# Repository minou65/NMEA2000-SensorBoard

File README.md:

# NMEA2000 Sensorboard

A universal PCB designed to support multiple NMEA 2000 sensor projects based on an ESP32 D1 Mini and an MCP2562 CAN bus transceiver. The board provides a 5 V regulated supply from the NMEA bus power line and exposes connectors for various sensors.

## Important Hint

Although the term NMEA2000 is used here, the software and device are **not certified NMEA2000 products** and have not passed any official approval process.
There is a possibility that the software or hardware does not fully comply with the NMEA2000 specification in all details.
If you connect this device to your NMEA2000 network, you do so at your own risk.

## Schema

> [!WARNING]
> When using Sensorboard v3, the DATA line of the DS1820 must be disconnected from IO36 and connected to IO22 instead. Otherwise, the DS1820 will not work.

## Supported Projects

The board can be used with the following firmware projects:

| Project | Description | Additional Components |
|---------|-------------|----------------------|
| [NMEA2000-DS1820](https://github.com/minou65/NMEA2000-DS1820) | Temperature monitor for up to 4 DS1820 sensors (−50 °C to +125 °C) with configurable alerts | X3–X6, R1 |
| [NMEA2000-FluidLevel](https://github.com/minou65/NMEA2000-FluidLevel) | Tank fill-level monitor using a VL53L0X time-of-flight sensor | X7, R1 |
| [NMEA2000-BME280](https://github.com/minou65/NMEA2000-BME280) | Environmental sensor for temperature, humidity and air pressure | X7 |
| [NMEA2000-BatteryMonitor](https://github.com/minou65/NMEA2000-BatteryMonitor) | Battery monitor using an INA226 (voltage, current, SoC, time-to-go) | X3, R1, IC4 |

Depending on the sensor type, additional external hardware may be required (for example sensors, shunt, cables, housings, adapters, or fuses). The exact requirements are documented in each corresponding project repository.

## Connector Overview

### X1 – Power Input (AK500/3, 3-pin)

| Pin | Signal | Description |
|-----|--------|-------------|
| 1 | NMEA Bus + / Battery + | Positive supply voltage |
| 2 | NMEA Bus - / Shunt - | Negative supply voltage or minus side of shunt |
| 3 | Shunt Load | Load side of shunt |

> **Note:** For all variants except the BatteryMonitor, X1 pin 1 and pin 2 are used. For the BatteryMonitor, all three X1 pins are required.  
> **BatteryMonitor:** NMEA + and NMEA - are not used for sensor supply. The sensor is powered directly from the measured battery via X1.  
> **Warning (BatteryMonitor):** Always install a fuse in the + line between the battery and the sensor board!

---

### X2 – CAN Bus (AK500/2, 2-pin)

| Pin | Signal | Wire colour |
|-----|--------|-------------|
| 1 | CANH | White |
| 2 | CANL | Blue |

---

### X3 – X6 – DS1820 Temperature Sensors (Molex 22-23-2031, 3-pin)

Same pinout on all four connectors. Each connector accepts one DS1820 sensor.  
All four connectors share a common OneWire bus (GPIO 18).

| Pin | Signal | Description |
|-----|--------|-------------|
| 1 | +3.3V | Sensor supply |
| 2 | DATA | OneWire data line |
| 3 | GND | Ground |

---

### X7 – I²C Bus (Molex 22-23-2041, 4-pin)

Used for VL53L0X (FluidLevel) and BME280 sensors.

| Pin | Signal | Description |
|-----|--------|-------------|
| 1 | +3.3V | Sensor supply |
| 2 | GND | Ground |
| 3 | SDA | I²C data (GPIO 21) |
| 4 | SCL | I²C clock (GPIO 22) |

## Supply and Voltage Levels

- Sensor connectors X3-X7 are 3.3 V level.
- For DS1820 on X3-X6: VCC is 3.3 V, DATA is OneWire, GND is pin 3.
- For I2C on X7: pin 1 is 3.3 V, pin 2 is GND, pin 3 is SDA, pin 4 is SCL.
- Board input power is connected via X1.
- In BatteryMonitor mode, supply is taken directly from the measured battery via X1 (not from NMEA + / -).
- Use an input voltage that is within the supported range of the regulator IC1 (R-78E05-1.0).

## Safety and Installation Notes

- Always verify polarity before first power-up.
- BatteryMonitor: install a fuse in the positive line close to the battery.
- BatteryMonitor: keep correct shunt orientation (battery side and load side) to avoid inverted current values.
- Never short the shunt terminals while the battery is connected.
- For high-current installations, use adequately dimensioned cables and secure screw terminals properly.

## Part List

| Part | Value | Device | Package | Notes |
|------|-------|--------|---------|-------|
| C1 | 47 µF / 25 V | CPOL-EUE5-8.5 | E5-8,5 | Bulk decoupling capacitor |
| C2 | 100 nF | C-EU050-024X044 | C050-024X044 | Bypass capacitor |
| D1 | 1N4001 | 1N4148 | SOD80 | Reverse-polarity protection diode |
| IC1 | R-78E05-1.0 | R-78E-XX1.0 | R-78E-XX1.0 | 5 V / 1 A switching regulator |
| IC2 | ESP32 D1 Mini | ESP32_D1_MINI | ESP32_D1_MINI | Main microcontroller |
| IC3 | MCP2562 | MCP2562SMD | SO-8 | CAN bus transceiver |
| IC4 ¹ | INA226 | INA226 | INA226 | Current / power monitor (BatteryMonitor only) |
| R1 ² | 4.7 kΩ / 270 Ω | R-EU_R0805 | R0805 | 4.7 kΩ OneWire pull-up (DS1820 / BatteryMonitor), 270 Ω for FluidLevel |
| X1 | — | AK500/3 | AK500/3 | Power input connector (3-pin, 2 used) |
| X2 | — | AK500/2 | AK500/2 | CAN bus connector |
| X3 ² | DS1820 | 22-23-2031 | 22-23-2031 | Sensor connector 1 (3-pin Molex) |
| X4 ³ | DS1820 | 22-23-2031 | 22-23-2031 | Sensor connector 2 (3-pin Molex) |
| X5 ³ | DS1820 | 22-23-2031 | 22-23-2031 | Sensor connector 3 (3-pin Molex) |
| X6 ³ | DS1820 | 22-23-2031 | 22-23-2031 | Sensor connector 4 (3-pin Molex) |
| X7 ⁴ | BUS | 22-23-2041 | 22-23-2041 | I²C bus connector (4-pin Molex) |

¹ BatteryMonitor only  
² DS1820, BatteryMonitor, and FluidLevel (270 Ω)  
³ DS1820 only (up to 4 sensors)  
⁴ FluidLevel and BME280  

## NMEA2000 Plug Pinout

Reference pinout for the NMEA2000 plug:

Typical NMEA2000 (Micro-C / DeviceNet) wire colors:

| Pin | Signal | Wire color |
|-----|--------|------------|
| 1 | Shield / Drain | Bare (uninsulated) |
| 2 | NET-S (+12 V bus supply) | Red |
| 3 | NET-C (GND) | Black |
| 4 | NET-H (CAN-H) | White |
| 5 | NET-L (CAN-L) | Blue |

## ESP32 D1 Mini Pin Configuration

| Pin | GPIO | Function |
|-----|------|----------|
| CAN Bus TX | GPIO 23 | MCP2562 TXD |
| CAN Bus RX | GPIO 5  | MCP2562 RXD |
| OneWire Data | GPIO 36 | DS1820 Data |

```cpp
#define ESP32_CAN_TX_PIN GPIO_NUM_23    // CAN Bus TX Pin
#define ESP32_CAN_RX_PIN GPIO_NUM_5     // CAN Bus RX Pin
#define ONE_WIRE_BUS     GPIO_NUM_36    // DS18B20 OneWire Data Pin
```

ESP32 D1 Mini pinout reference:

## Component Selection by Variant

| Component | All variants | DS1820 | FluidLevel | BME280 | BatteryMonitor |
|-----------|:-----------:|:------:|:----------:|:------:|:--------------:|
| C1, C2    | ✓ | ✓ | ✓ | ✓ | ✓ |
| D1        | ✓ | ✓ | ✓ | ✓ | ✓ |
| IC1       | ✓ | ✓ | ✓ | ✓ | ✓ |
| IC2       | ✓ | ✓ | ✓ | ✓ | ✓ |
| IC3       | ✓ | ✓ | ✓ | ✓ | ✓ |
| X1 (2-pin)| ✓ | ✓ | ✓ | ✓ | ✓ (3-pin) |
| X2        | ✓ | ✓ | ✓ | ✓ | ✓ |
| R1        |   | ✓ | ✓ |   | ✓ |
| X3        |   | ✓ |   |   | ✓ |
| X4–X6     |   | ✓ |   |   |   |
| X7        |   |   | ✓ | ✓ |   |
| IC4       |   |   |   |   | ✓ |

## License

GPL-3.0 – see [LICENSE](LICENSE)

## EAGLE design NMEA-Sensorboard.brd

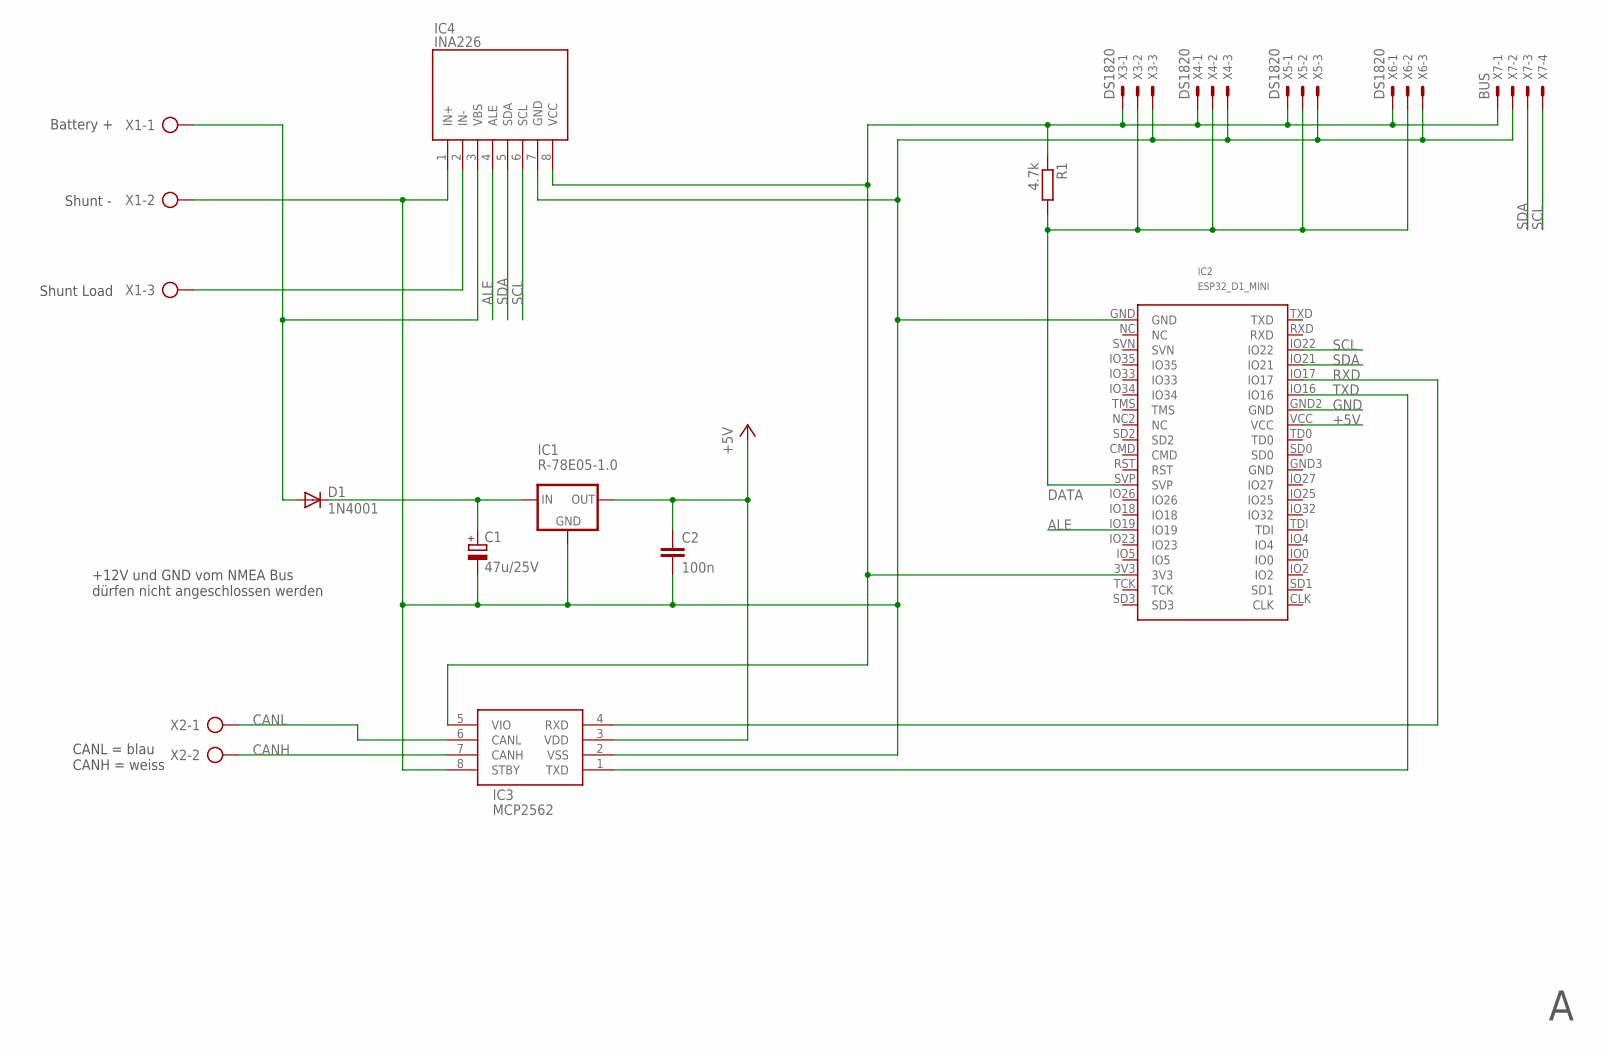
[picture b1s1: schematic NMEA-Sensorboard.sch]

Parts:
C1: 47u/25V; E2-5
C2: 100n; C050-024X044
D1: 1N4001; SOD80
IC1: R-78E05-1.0; R-78E-XX1.0
IC2: ESP32_D1_MINI
IC3: MCP2562; SO-8
IC4: INA226
R1: 4.7k; R0805
X1: AK500/3
X2: AK500/2
X3, X4, X5, X6: DS1820; 22-23-2031
X7: BUS; 22-23-2041

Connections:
12V: D1.A, IC4.3 (VBS), X1.1
+3V3: IC2.3V3, IC3.5 (VIO), IC4.8 (VCC), R1.1, X3.1, X4.1, X5.1, X6.1, X7.1
+5V: C2.1, IC1.OUT, IC2.VCC, IC3.3 (VDD)
ALE: IC2.IO19, IC4.4 (ALE)
CANH: IC3.7 (CANH), X2.2
CANL: IC3.6 (CANL), X2.1
DATA: IC2.SVP, R1.2, X3.2, X4.2, X5.2, X6.2
GND: C1.-, C2.2, IC1.GND, IC2.GND, IC2.GND2 (GND), IC3.2 (VSS), IC3.8 (STBY), IC4.1 (IN+), IC4.7 (GND), X1.2, X3.3, X4.3, X5.3, X6.3, X7.2
LOAD: IC4.2 (IN-), X1.3
unnamed: C1.+, D1.C, IC1.IN
RXD: IC2.IO17, IC3.4 (RXD)
SCL: IC2.IO22, IC4.6 (SCL), X7.4
SDA: IC2.IO21, IC4.5 (SDA), X7.3
TXD: IC2.IO16, IC3.1 (TXD)

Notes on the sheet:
CANL = blau CANH = weiss
Shunt -
Shunt Load
Battery +
+12V und GND vom NMEA Bus dürfen nicht angeschlossen werden

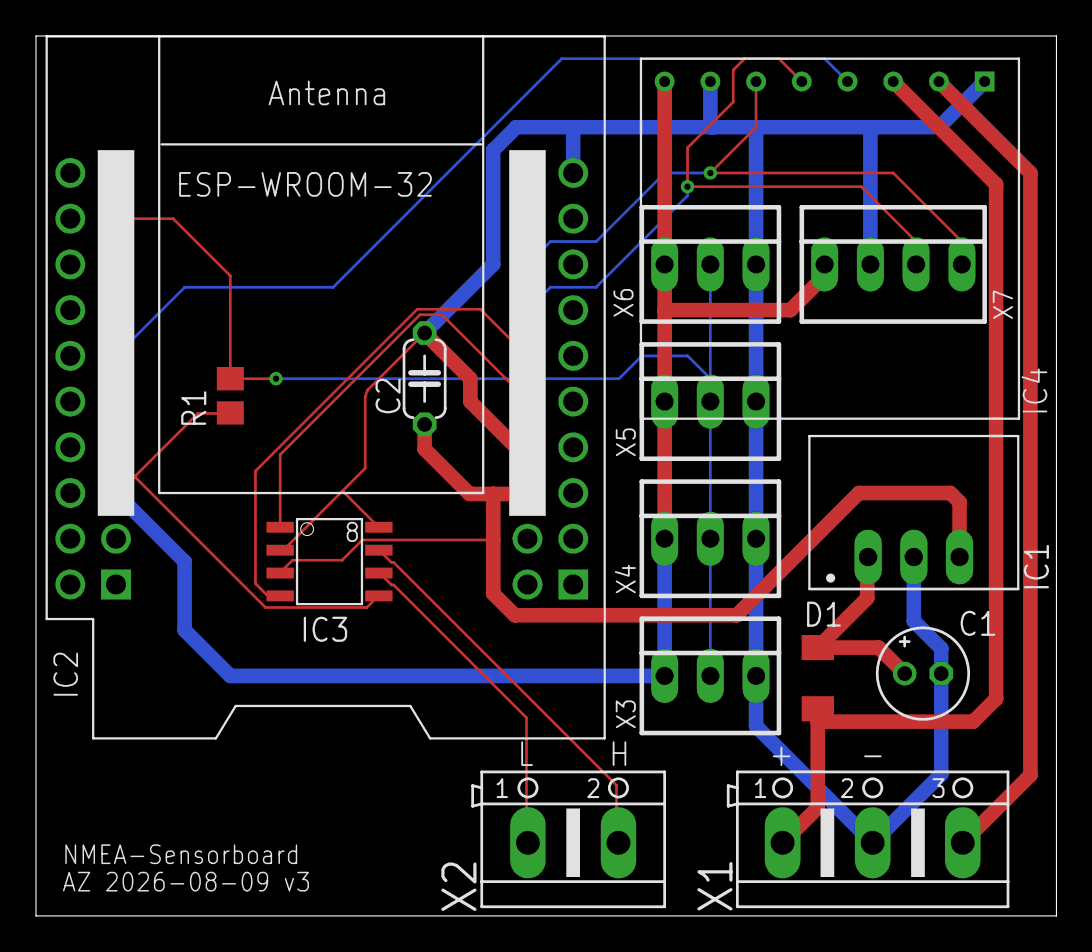
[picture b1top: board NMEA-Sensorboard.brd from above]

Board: 2 copper layers, 56.7 x 48.9 mm, 15 parts (0 on the bottom side), 14 nets.

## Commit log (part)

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2026-06-10 Add initial files for NMEA2000 Sensorboard project
    - Added schematic image (NMEA2000-Sensorboard.png)
    - Created part list (Partlist) detailing components used
    - Added README.md with project overview, supported projects, connector details, supply information, safety notes, and component selection by variant
2026-06-22 Add ESP32 D1 Mini pinout reference to README
2026-06-22 initial version
2026-06-22 Update GPIO pin assignments for DS1820 sensor in README
2026-06-24 Sensor oun changed
